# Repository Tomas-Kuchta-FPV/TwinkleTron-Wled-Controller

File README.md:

# LED Pixel Driver (TwinkleTron)

>Toto je anglická verze souboru README. Český překlad je [zde](CZ/README.md).

This project is an open-source controller for addressable LED strips, combining a wide range of features such as power measurement, IR sensors, and easy integration into various installations. The project is designed with a focus on low power consumption and user safety.

Includes:

- **ESP32-C3-WROOM-02** as the main processor.
- Integrated power measurement (ACS722 and voltage divider).
- Relay for LED power control.
- Surge and ESD protection.

## Table of Contents

0. [Introduction](#led-pixel-driver)
1. [What makes this project interesting?](#what-makes-this-project-interesting)
2. [Features](#features)
3. [Why did I decide to create this project?](#why-did-i-decide-to-create-this-project)
4. [Development](#development)
5. [Documentation](#documentation)
6. [Would I like to sell it?](#would-i-like-to-sell-it)
7. [What is my motivation?](#what-is-my-motivation)
8. [What have I learned?](#what-have-i-learned)
9. [What is its actual use?](#what-is-its-actual-use)
10. [Software](#software)
11. [Conclusion](#conclusion)
12. [Contributions](#contributions)
13. [License](#license)

### Status

- **Version**: 2.0 in the works. Evherything should be ready to order and test.

## What Makes This Project Interesting?

Power measurement!  
I wanted to know how much energy I was consuming, so I decided to use ACS722 and a voltage divider. However, I haven’t seen a similar project that includes this kind of measurement.

## Features

- ESP32-C3-WROOM-02
- Onboard relay for minimal standby current
- Integrated 10A fuse for LED strip protection
- Power measurement using WLED usermod (ACS722, voltage divider)
- Input for an external button
- Temperature sensor
- IR sensor

<details>
    <summary>Show More</summary>
    <ul>
        <li>Easy-to-use screw terminals (default)</li>
        <li>Compatible with PhoenixContact PCB connector</li>
        <li>ESP protection (PTC resettable fuse, ESD protection, diodes)</li>
        <li>Surge protection for 5V and 3.3V</li>
        <li>Boot button can be used as a WLED button</li>
        <li>Buck converter powered from Vin</li>
        <li>Unused GPIOs are exposed on the board</li>
        <li>USB-C connector</li>
        <li>5V logic output</li>
    </ul>
</details>

## Why Did I Decide to Create This Project?

I wanted to build something of my own—something I could improve and customize as needed. I also wanted to contribute to the open-source community and to create something properly designed.  
This project includes several motivations:

- **Power measurement**: To monitor energy consumption.
- **Relay**: To disconnect LED strips.
- **Low standby power**: To minimize energy usage in standby mode.
- **Ease of integration**: To simplify use in various installations.
- **To learn**: To gain experience with new technologies.
- **To share**: To contribute to the open-source community.
- **To create something nice**:  To have a functional and visually appealing solution.

## Development

I've been working on this project for quite a while.

The first prototype didn’t look great, but it worked well despite forgetting to power the SN74AHCT125 IC—something I fixed with a solder bridge.

Version V0.31 was the first to include all desired features but had a few bugs.

V1.0 was the first fully functional version but still had issues, like components on both sides of the PCB causing assembly difficulties and a suboptimal USB-voltage mixer.

V2.0 addressed all known issues and is fully functional. It is still in development, but it feels complete—though you never know what might come up. 😅

## Documentation

A great beginer video can be found here [YouTube](https://www.youtube.com/watch?v=FvPuiWTE6ic).

KiCad files are in the [Board](Board/) directory.

Schematics and PCB layouts are in the [Documentation](Documentation/) directory.  
And the [Builds](Builds/) directory contains the binary for the ESP32-C3.

The enclosure is in the [Case](Case/) directory.  
Photos of the completed project are in the [Images](Images/) directory.

## Would I Like to Sell It?

Yes, in the near future, I would like to sell this project as a finished product so that everyone can use this controller.  
It would also enable me to continue its development and create interesting new projects.

## What Is My Motivation?

- Installing LED strips in 2021.
- Problems with ESP32 (damaged power, failed updates).
- Creating a robust and user-friendly solution.

<details>
<summary>More</summary>
In 2021, I installed addressable LED strips for the first time and was amazed. However, working with bare ESP32 boards came with problems. My first controller released "magic smoke" after I accidentally applied 12V to a GPIO pin. The second ESP32 got damaged while fixing an update while still powered. These experiences inspired me to start this project.
</details>

## What Have I Learned?

I’ve learned a lot, including:

- PCB design  

<details>
<summary>More</summary>

- Using ACS722  
- Using a voltage divider  
- Using an IR sensor  
- Using a temperature sensor  
- Using a relay  
- Using a USB-C connector  
- Using a buck converter  
- Using ESP32-C3  
- Using WLED  
- Using PlatformIO  
- Using ESP-IDF  

I learned how to combine all these into a functional solution—and I enjoyed the process. 😀
</details>

## What Is Its Actual Use?

- **Controlling addressable LEDs**: Precise control of individual LEDs.
- **LED light shows**: Ideal for creating dynamic effects.  
- **Holiday decorations**: Perfect for festive displays.  
- **Easy integration**: Fits into various DIY projects.  
- **Smart home**: Great for lighting automation.

## Software

I use the `WLED` project, which is very user-friendly and feature-rich. You can download the binary [here](Builds/). My usermod is included in [GitHub PR #4108](https://github.com/Aircoookie/WLED/pull/4108). Apologies for any mistakes—I appreciate feedback. Also, I’m not experienced with Git, so I welcome patience with any errors in my PRs.

## Conclusion

This project has been both a challenge and an opportunity to push my skills forward. I’ve learned many new technologies and methods while creating a functional solution I’m proud of. The process confirmed that sharing knowledge and embracing open technologies hold great potential.

I hope this project inspires others and saves time for their own ideas. I welcome feedback, improvement suggestions, or support to continue developing this project.

Thank you for your interest I’m excited about what the future holds!

### Why Am I Doing This?

Honestly, I’m not sure I just felt inspired and supported by my family! This open-source project was born from that.

## Contributions

If you have ideas for improvements or spot errors, feel free to open a pull request or issue. All help is welcome. :)  
If anyone would like to participate in the development, I would be glad for any help. 😊  
And if anyone would like to support me financially for further development not just this project, I will be glad for any help. 😊

## License

The project is currently licensed under **CC BY-NC-SA 4.0**, allowing sharing and modifications for non-commercial use. A future transition to **CERN-OHL-S** is planned after recovering development costs.

**CC BY-NC-SA 4.0** [(CC)](https://creativecommons.org/licenses/by-nc-sa/4.0/deed.en) **→** **CERN-OHL-S** [(OSI Approved OSHW License)](https://opensource.org/license/cern-ohl-s)

Shield: [![CC BY-NC-SA 4.0][cc-by-nc-sa-shield]][cc-by-nc-sa]

This work is licensed under a
[Creative Commons Attribution-NonCommercial-ShareAlike 4.0 International License][cc-by-nc-sa].

[![CC BY-NC-SA 4.0][cc-by-nc-sa-image]][cc-by-nc-sa]

[cc-by-nc-sa]: http://creativecommons.org/licenses/by-nc-sa/4.0/
[cc-by-nc-sa-image]: https://licensebuttons.net/l/by-nc-sa/4.0/88x31.png
[cc-by-nc-sa-shield]: https://img.shields.io/badge/License-CC%20BY--NC--SA%204.0-lightgrey.svg

#### Disclaimer (No Warranty)

This licensed work is provided "as is," without any warranties, including implied warranties of merchantability or fitness for a particular purpose. The author(s) and copyright holder(s) bear no liability for claims, damages, or other liabilities.

#### AI Assistance

I used AI to assist with translation and grammar corrections. Thank you for understanding.

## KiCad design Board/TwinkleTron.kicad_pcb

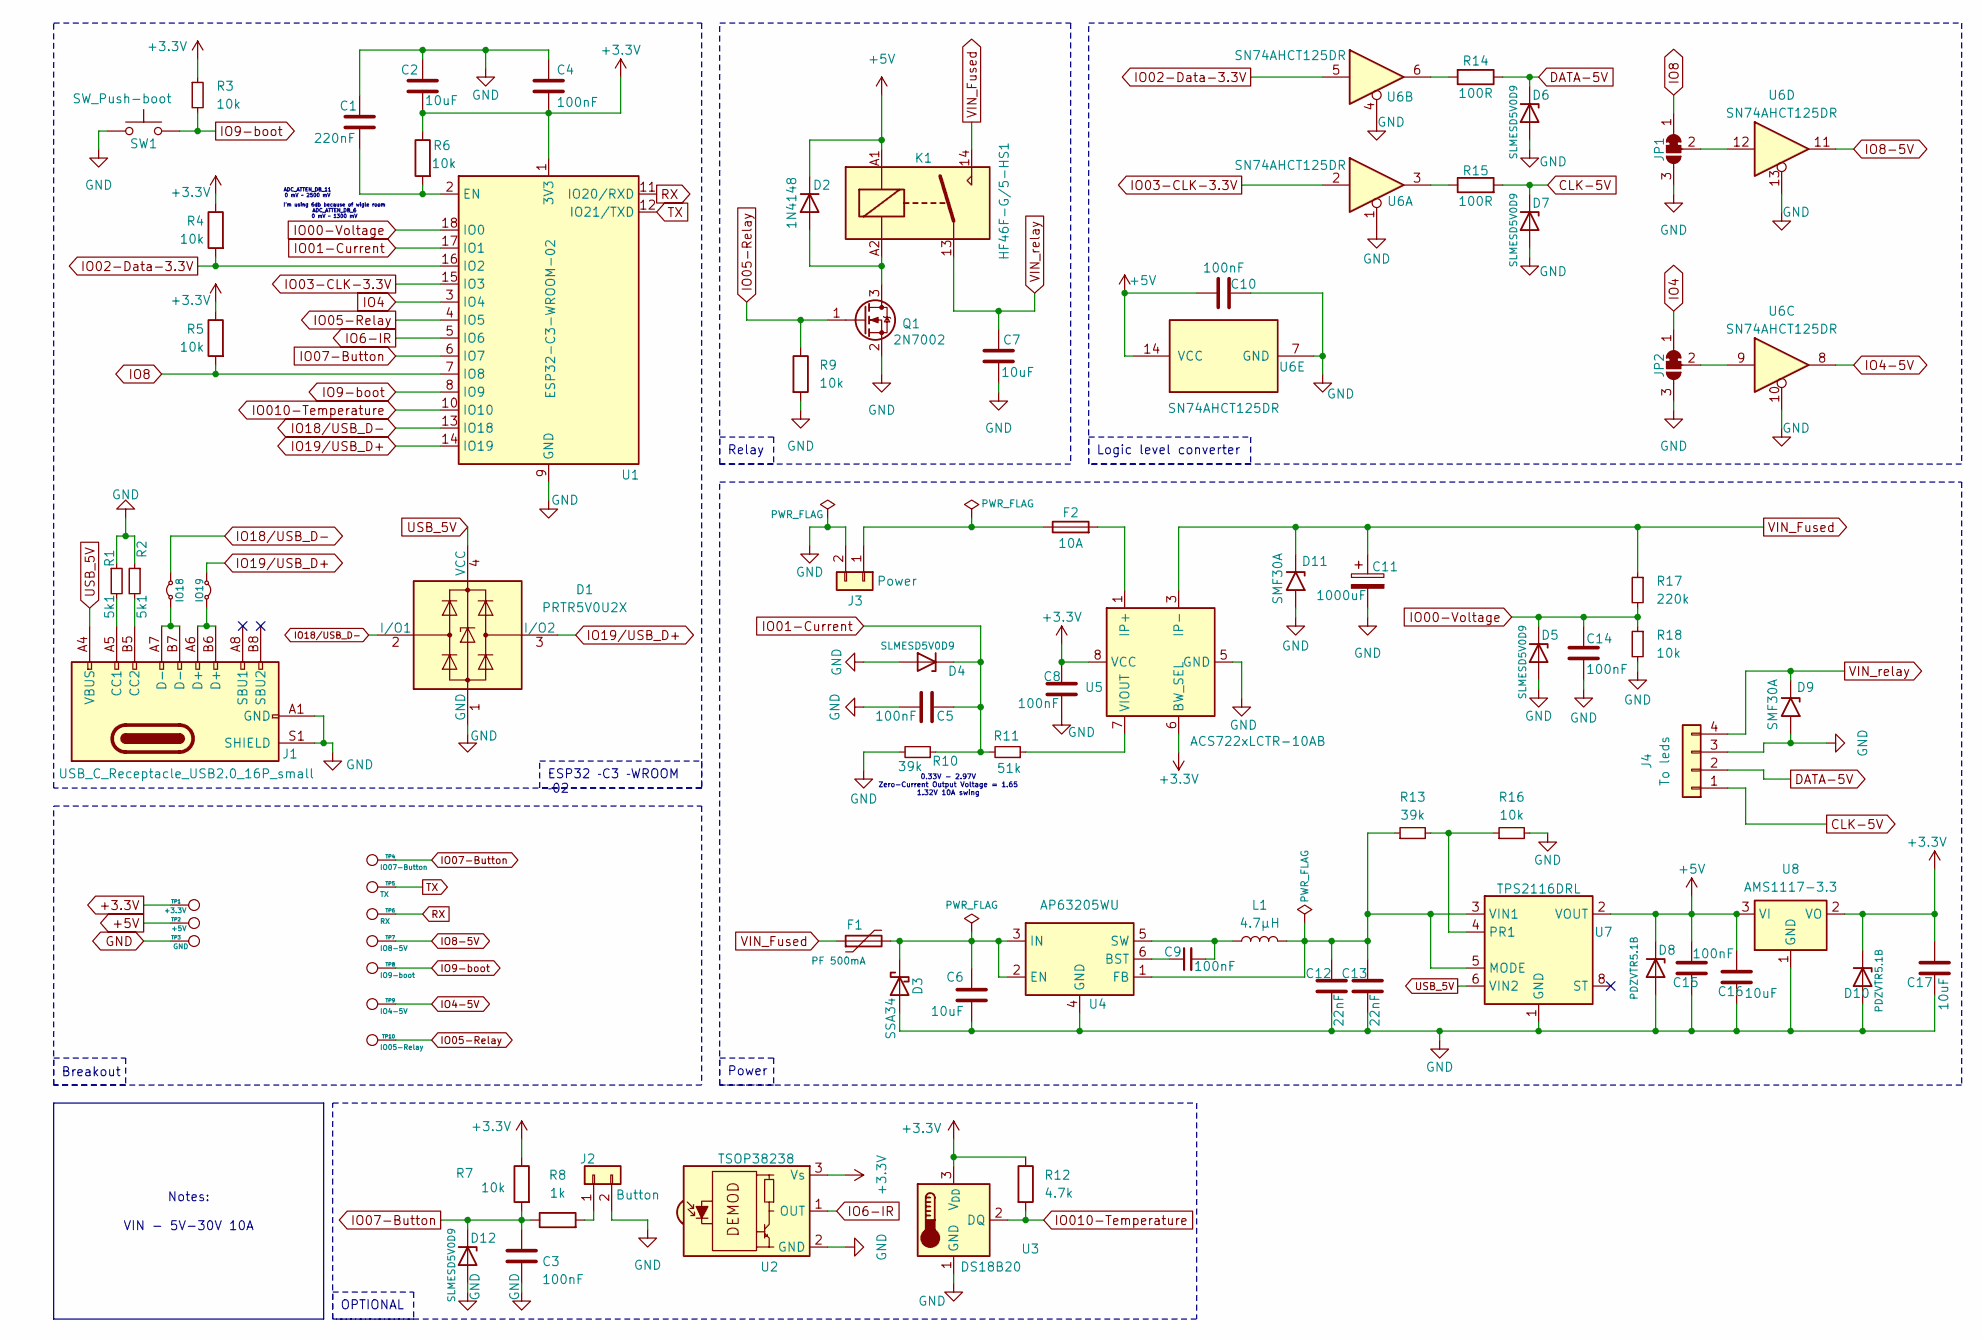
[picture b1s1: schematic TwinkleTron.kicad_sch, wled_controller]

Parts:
C1: 220nF; C_0603_1608Metric_Pad1.08x0.95mm_HandSolder; LCSC C6119866
C2, C6, C16, C17: 10uF; C_0603_1608Metric_Pad1.08x0.95mm_HandSolder; LCSC C22367827
C3, C4, C5, C8, C9, C10, C14, C15: 100nF; C_0603_1608Metric_Pad1.08x0.95mm_HandSolder; LCSC C66501
C7: 10uF; C_0603_1608Metric_Pad1.08x0.95mm_HandSolder; LCSC C194427
C11: 1000uF; CP_Radial_D10.0mm_P5.00mm_laying; LCSC C398835
C12, C13: 22nF; C_0603_1608Metric_Pad1.08x0.95mm_HandSolder; LCSC C519429
D1: PRTR5V0U2X; SOT-143; LCSC C2827688
D2: 1N4148; D_SOD-323; LCSC C2128
D3: SSA34; D_SMA; LCSC C466998
D4, D5, D6, D7, D12: SLMESD5V0D9; D_SOD-323; LCSC C19170915
D8, D10: PDZVTR5.1B; D_SOD-128; LCSC C253499
D9, D11: SMF30A; D_SMF; LCSC C19077518
F1: PF 500mA; R_1206_3216Metric_Pad1.30x1.75mm_HandSolder; LCSC C720075
F2: 10A; Fuseholder_Littelfuse_Nano2_154x; LCSC C206921
IO18, IO19: Jumper_2_Small_Bridged; SolderJumper-2_P1.3mm_Bridged_RoundedPad1.0x1.5mm
J1: USB_C_Receptacle_USB2.0_16P_small; USB_C_Receptacle_HRO_TYPE-C-31-M-12; LCSC C165948
J2: Button; PinHeader_1x02_P2.54mm_Horizontal; LCSC C492410
J3: Power; TerminalBlock_Phoenix_MKDS-3-2-5.08_1x02_P5.08mm_Horizontal; LCSC C2915639
J4: To leds; TerminalBlock_Phoenix_MKDS-3-4-5.08_1x04_P5.08mm_Horizontal; LCSC C2915641
JP1, JP2: SolderJumper_3_Bridged12; SolderJumper-3_P1.3mm_Bridged12_RoundedPad1.0x1.5mm_NumberL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
K1: HF46F-G/5-HS1; RELAY_HF46F_005-HS1; LCSC C165255
L1: 4.7µH; L_1008_2520Metric; Mfr. Part # FTC252010S4R7MBCA; LCSC C5832360
Q1: 2N7002; SOT-23; LCSC C8545
R1, R2: 5k1; R_0603_1608Metric_Pad0.98x0.95mm_HandSolder; LCSC C23186
R3, R4, R5, R6, R7, R9, R16, R18: 10k; R_0603_1608Metric_Pad0.98x0.95mm_HandSolder; LCSC C25804
R8: 1k; R_0603_1608Metric_Pad0.98x0.95mm_HandSolder; LCSC C21190
R10, R13: 39k; R_0603_1608Metric_Pad0.98x0.95mm_HandSolder; LCSC C23153
R11: 51k; R_0603_1608Metric_Pad0.98x0.95mm_HandSolder; LCSC C23196
R12: 4.7k; R_0603_1608Metric_Pad0.98x0.95mm_HandSolder; LCSC C23162
R14, R15: 100R; R_0603_1608Metric_Pad0.98x0.95mm_HandSolder; LCSC C22775
R17: 220k; R_0603_1608Metric_Pad0.98x0.95mm_HandSolder; LCSC C22961
SW1: SW_Push-boot; SW_Push_SPST_NO_Alps_SKRK; LCSC C115357
TP1: +3.3V; TestPoint_Pad_D1.5mm_SM
TP2: +5V; TestPoint_Pad_D1.5mm_SM
TP3: GND; TestPoint_Pad_D1.5mm_SM
TP4: IO07-Button; TestPoint_Pad_D1.5mm_SM
TP5: TX; TestPoint_Pad_D1.5mm_SM
TP6: RX; TestPoint_Pad_D1.5mm_SM
TP7: IO8-5V; TestPoint_Pad_D1.5mm_SM
TP8: IO9-boot; TestPoint_Pad_D1.5mm_SM
TP9: IO4-5V; TestPoint_Pad_D1.5mm_SM
TP10: IO05-Relay; TestPoint_Pad_D1.5mm_SM
U1: ESP32-C3-WROOM-02; ESP32-C3-WROOM-02-Aisler_DR; LCSC C2934560
U2: TSOP38238; Vishay_MINICAST-3Pin; LCSC C141632
U3: DS18B20; TO-92_Inline_Wide; LCSC C376006
U4: AP63205WU; TSOT-23-6; LCSC C2071056
U5: ACS722xLCTR-10AB; SOIC-8_3.9x4.9mm_P1.27mm; LCSC C459316
U6: SN74AHCT125DR; SOIC-14_3.9x8.7mm_P1.27mm; LCSC C155176
U7: TPS2116DRL; SOT-583-8; LCSC C3235557
U8: AMS1117-3.3; SOT-89-3; LCSC C880752

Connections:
+3.3V: C2.2, C4.2, C8.1, C17.1, D10.1 (K), R3.1, R4.1, R5.1, R6.1, R7.1, R12.1, TP1.1, U1.1 (3V3), U2.3 (Vs), U3.3 (V_{DD}), U5.6 (BW_SEL), U5.8 (VCC), U8.2 (VO)
+5V: C10.2, C15.1, C16.1, D2.1 (K), D8.1 (K), K1.A1, TP2.1, U6.14 (VCC), U7.2 (VOUT), U7.7 (VOUT), U8.3 (VI)
CLK-5V: D7.1 (K), J4.1, R15.2
DATA-5V: D6.1 (K), J4.2, R14.1
GND: C1.1, C2.1, C3.2, C4.1, C5.2, C6.2, C7.2, C8.2, C10.1, C11.2, C12.2, C13.2, C14.2, C15.2, C16.2, C17.2, D1.1 (GND), D3.2 (A), D4.2 (A), D5.2 (A), D6.2 (A), D7.2 (A), D8.2 (A), D9.2 (A2), D10.2 (A), D11.2 (A2), D12.2 (A), J1.A1 (GND), J1.A12 (GND), J1.B1 (GND), J1.B12 (GND), J1.S1 (SHIELD), J2.2, J3.2, J4.3, JP1.3 (B), JP2.3 (B), Q1.2 (S), R1.1, R2.1, R9.2, R10.2, R16.2, R18.2, SW1.1, TP3.1, U1.9 (GND), U1.19 (GND), U2.2 (GND), U3.1 (GND), U4.4 (GND), U5.5 (GND), U6.1, U6.4, U6.7 (GND), U6.10, U6.13, U7.1 (GND), U8.1 (GND)
IO00-Voltage: C14.1, D5.1 (K), R17.2, R18.1, U1.18 (IO0)
IO01-Current: C5.1, D4.1 (K), R10.1, R11.2, U1.17 (IO1)
IO02-Data-3.3V: R4.2, U1.16 (IO2), U6.5
IO03-CLK-3.3V: U1.15 (IO3), U6.2
IO4: JP2.1 (A), U1.3 (IO4)
IO4-5V: TP9.1, U6.8
IO05-Relay: Q1.1 (G), R9.1, TP10.1, U1.4 (IO5)
IO6-IR: U1.5 (IO6), U2.1 (OUT)
IO07-Button: C3.1, D12.1 (K), R7.2, R8.1, TP4.1, U1.6 (IO7)
IO8: JP1.1 (A), R5.2, U1.7 (IO8)
IO8-5V: TP7.1, U6.11
IO9-boot: R3.2, SW1.2, TP8.1, U1.8 (IO9)
IO010-Temperature: R12.2, U1.10 (IO10), U3.2 (DQ)
IO18/USB_D-: D1.2 (I/O1), IO18.2 (B), U1.13 (IO18)
IO19/USB_D+: D1.3 (I/O2), IO19.2 (B), U1.14 (IO19)
unnamed: D2.2 (A), K1.A2, Q1.3 (D)
unnamed: C6.1, D3.1 (K), F1.2, U4.2 (EN), U4.3 (IN)
unnamed: F2.2, U5.1 (IP+), U5.2 (IP+)
unnamed: IO18.1 (A), J1.A7 (D-), J1.B7 (D-)
unnamed: IO19.1 (A), J1.A6 (D+), J1.B6 (D+)
unnamed: J1.A5 (CC1), R1.2
unnamed: J1.B5 (CC2), R2.2
unnamed: J2.1, R8.2
unnamed: F2.1, J3.1
unnamed: JP1.2 (C), U6.12
unnamed: JP2.2 (C), U6.9
unnamed: R14.2, U6.6
unnamed: R15.1, U6.3
unnamed: C1.2, R6.2, U1.2 (EN)
unnamed: C9.1, U4.6 (BST)
unnamed: C12.1, C13.1, L1.2, R13.1, U4.1 (FB), U7.3 (VIN1), U7.5 (MODE)
unnamed: C9.2, L1.1, U4.5 (SW)
unnamed: R11.1, U5.7 (VIOUT)
unnamed: R13.2, R16.1, U7.4 (PR1)
RX: TP6.1, U1.11 (IO20/RXD)
TX: TP5.1, U1.12 (IO21/TXD)
USB_5V: D1.4 (VCC), J1.A4 (VBUS), J1.A9 (VBUS), J1.B4 (VBUS), J1.B9 (VBUS), U7.6 (VIN2)
VIN_Fused: C11.1, D11.1 (A1), F1.1, K1.14, R17.1, U5.3 (IP-), U5.4 (IP-)
VIN_relay: C7.1, D9.1 (A1), J4.4, K1.13

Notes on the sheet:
Notes: VIN - 5V-30V 10A
Relay
Breakout
ESP32 ­C3 ­WROOM ­02
Power
OPTIONAL
Logic level converter
ADC_ATTEN_DB_11 0 mV ~ 2500 mV
0.33V - 2.97V Zero-Current Output Voltage = 1.65 1.32V 10A swing
I'm using 6db because of wigle room ADC_ATTEN_DB_6 0 mV ~ 1300 mV

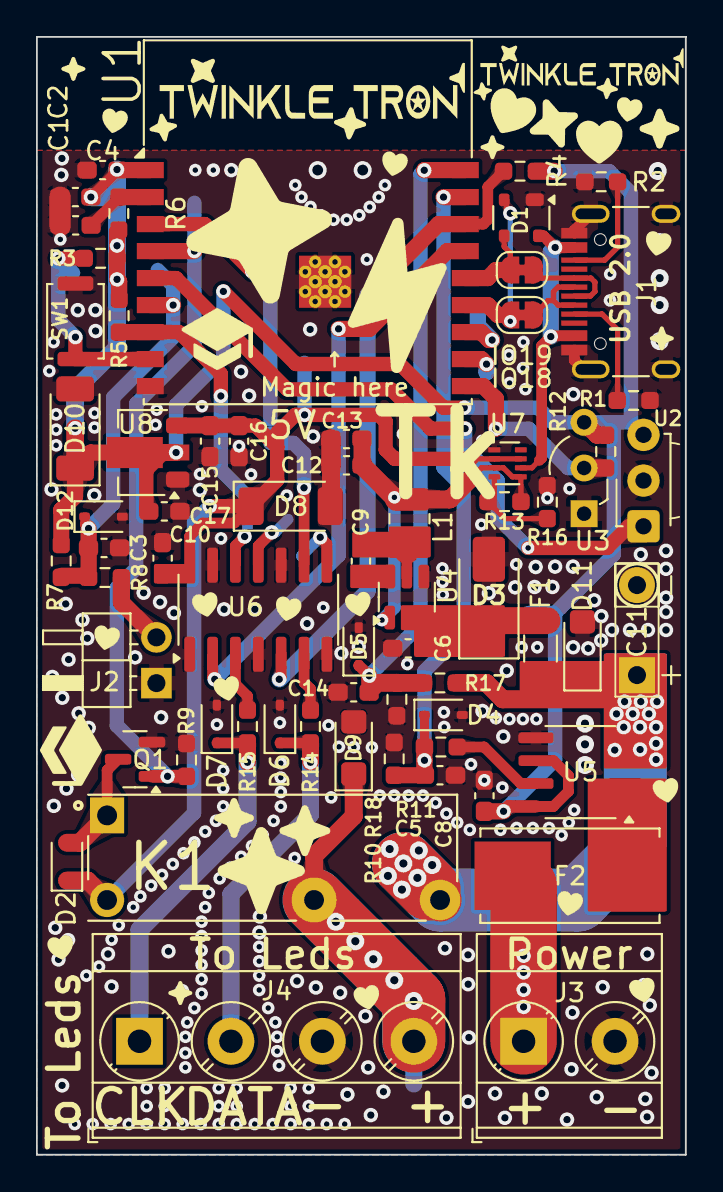
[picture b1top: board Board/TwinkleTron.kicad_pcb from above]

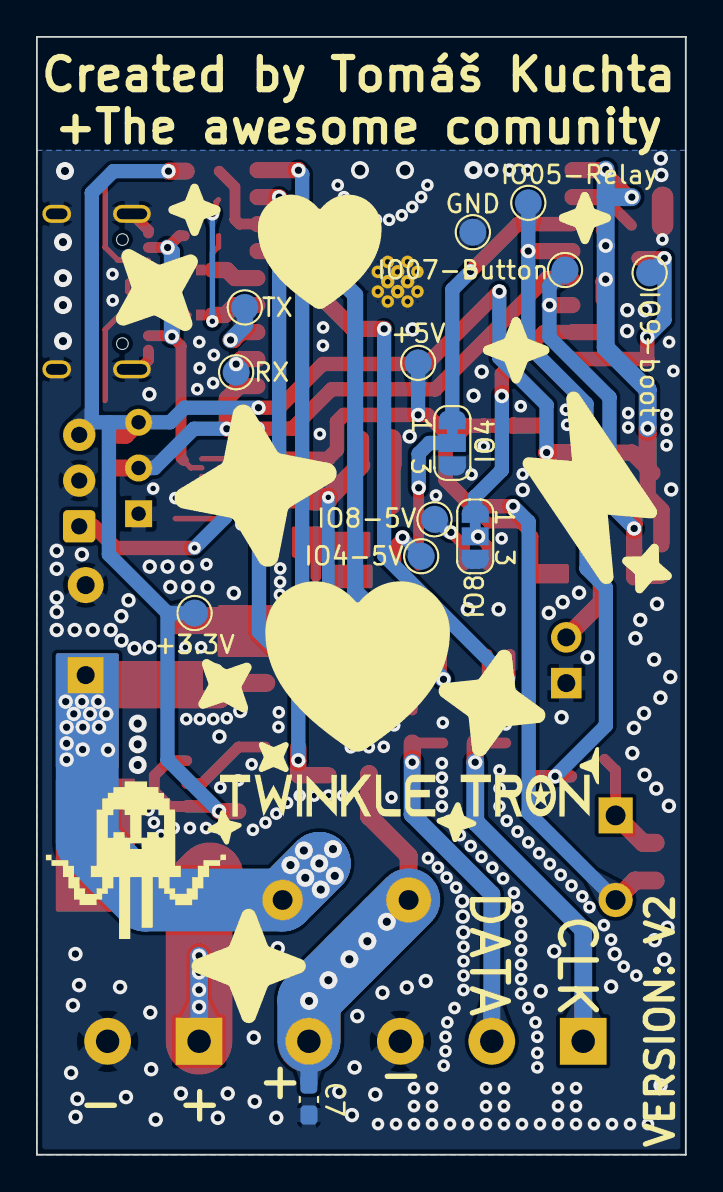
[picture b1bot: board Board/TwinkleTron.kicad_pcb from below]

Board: 2 copper layers, 36.0 x 62.1 mm, 83 parts (15 on the bottom side), 44 nets.

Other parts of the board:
akemi001: LOGO; akemi
logo1, logo2, logo3: LOGO; logo

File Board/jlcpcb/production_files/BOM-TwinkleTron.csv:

Comment,Designator,Footprint,LCSC
TSOP38238,U2,Vishay_MINICAST-3Pin,C141632
SN74AHCT125DR,U6,SOIC-14_3.9x8.7mm_P1.27mm,C155176
HF46F-G/5-HS1,K1,RELAY_HF46F_005-HS1,C165255
USB_C_Receptacle_USB2.0_16P_small,J1,USB_C_Receptacle_HRO_TYPE-C-31-M-12,C165948
SMF30A,D9,D_SMF,C19077518
SLMESD5V0D9,"D4,D5,D6,D7",D_SOD-323,C19170915
10uF,C7,C_0603_1608Metric_Pad1.08x0.95mm_HandSolder,C194427
10A,F2,Fuseholder_Littelfuse_Nano2_154x,C206921
AP63205WU,U4,TSOT-23-6,C2071056
1k,R8,R_0603_1608Metric_Pad0.98x0.95mm_HandSolder,C21190
1N4148,D2,D_SOD-323,C2128
10uF,"C16,C17,C2,C6",C_0603_1608Metric_Pad1.08x0.95mm_HandSolder,C22367827
100R,"R14,R15",R_0603_1608Metric_Pad0.98x0.95mm_HandSolder,C22775
220k,R17,R_0603_1608Metric_Pad0.98x0.95mm_HandSolder,C22961
39k,"R10,R13",R_0603_1608Metric_Pad0.98x0.95mm_HandSolder,C23153
4.7k,R12,R_0603_1608Metric_Pad0.98x0.95mm_HandSolder,C23162
5k1,"R1,R2",R_0603_1608Metric_Pad0.98x0.95mm_HandSolder,C23186
51k,R11,R_0603_1608Metric_Pad0.98x0.95mm_HandSolder,C23196
PDZVTR5.1B,"D10,D8",D_SOD-128,C253499
10k,"R16,R18,R3,R4,R5,R6,R7,R9",R_0603_1608Metric_Pad0.98x0.95mm_HandSolder,C25804
PRTR5V0U2X,D1,SOT-143,C2827688
Power,J3,TerminalBlock_Phoenix_MKDS-3-2-5.08_1x02_P5.08mm_Horizontal,C2915639
To leds,J4,TerminalBlock_Phoenix_MKDS-3-4-5.08_1x04_P5.08mm_Horizontal,C2915641
ESP32-C3-WROOM-02,U1,ESP32-C3-WROOM-02-Aisler_DR,C2934560
TPS2116DRL,U7,SOT-583-8,C3235557
DS18B20,U3,TO-92_Inline_Wide,C376006
1000uF,C11,CP_Radial_D10.0mm_P5.00mm_laying,C398835
ACS722xLCTR-10AB,U5,SOIC-8_3.9x4.9mm_P1.27mm,C459316
SSA34,D3,D_SMA,C466998
Button,J2,PinHeader_1x02_P2.54mm_Horizontal,C492410
22nF,"C12,C13",C_0603_1608Metric_Pad1.08x0.95mm_HandSolder,C519429
4.7µH,L1,L_1008_2520Metric,C5832360
220nF,C1,C_0603_1608Metric_Pad1.08x0.95mm_HandSolder,C6119866
100nF,"C10,C14,C15,C3,C4,C5,C8,C9",C_0603_1608Metric_Pad1.08x0.95mm_HandSolder,C66501
PF 500mA,F1,R_1206_3216Metric_Pad1.30x1.75mm_HandSolder,C720075
AMS1117-3.3,U8,SOT-89-3,C880752
SW_Push-boot,SW1,SW_Push_SPST_NO_Alps_SKRK,
2N7002,Q1,SOT-23,

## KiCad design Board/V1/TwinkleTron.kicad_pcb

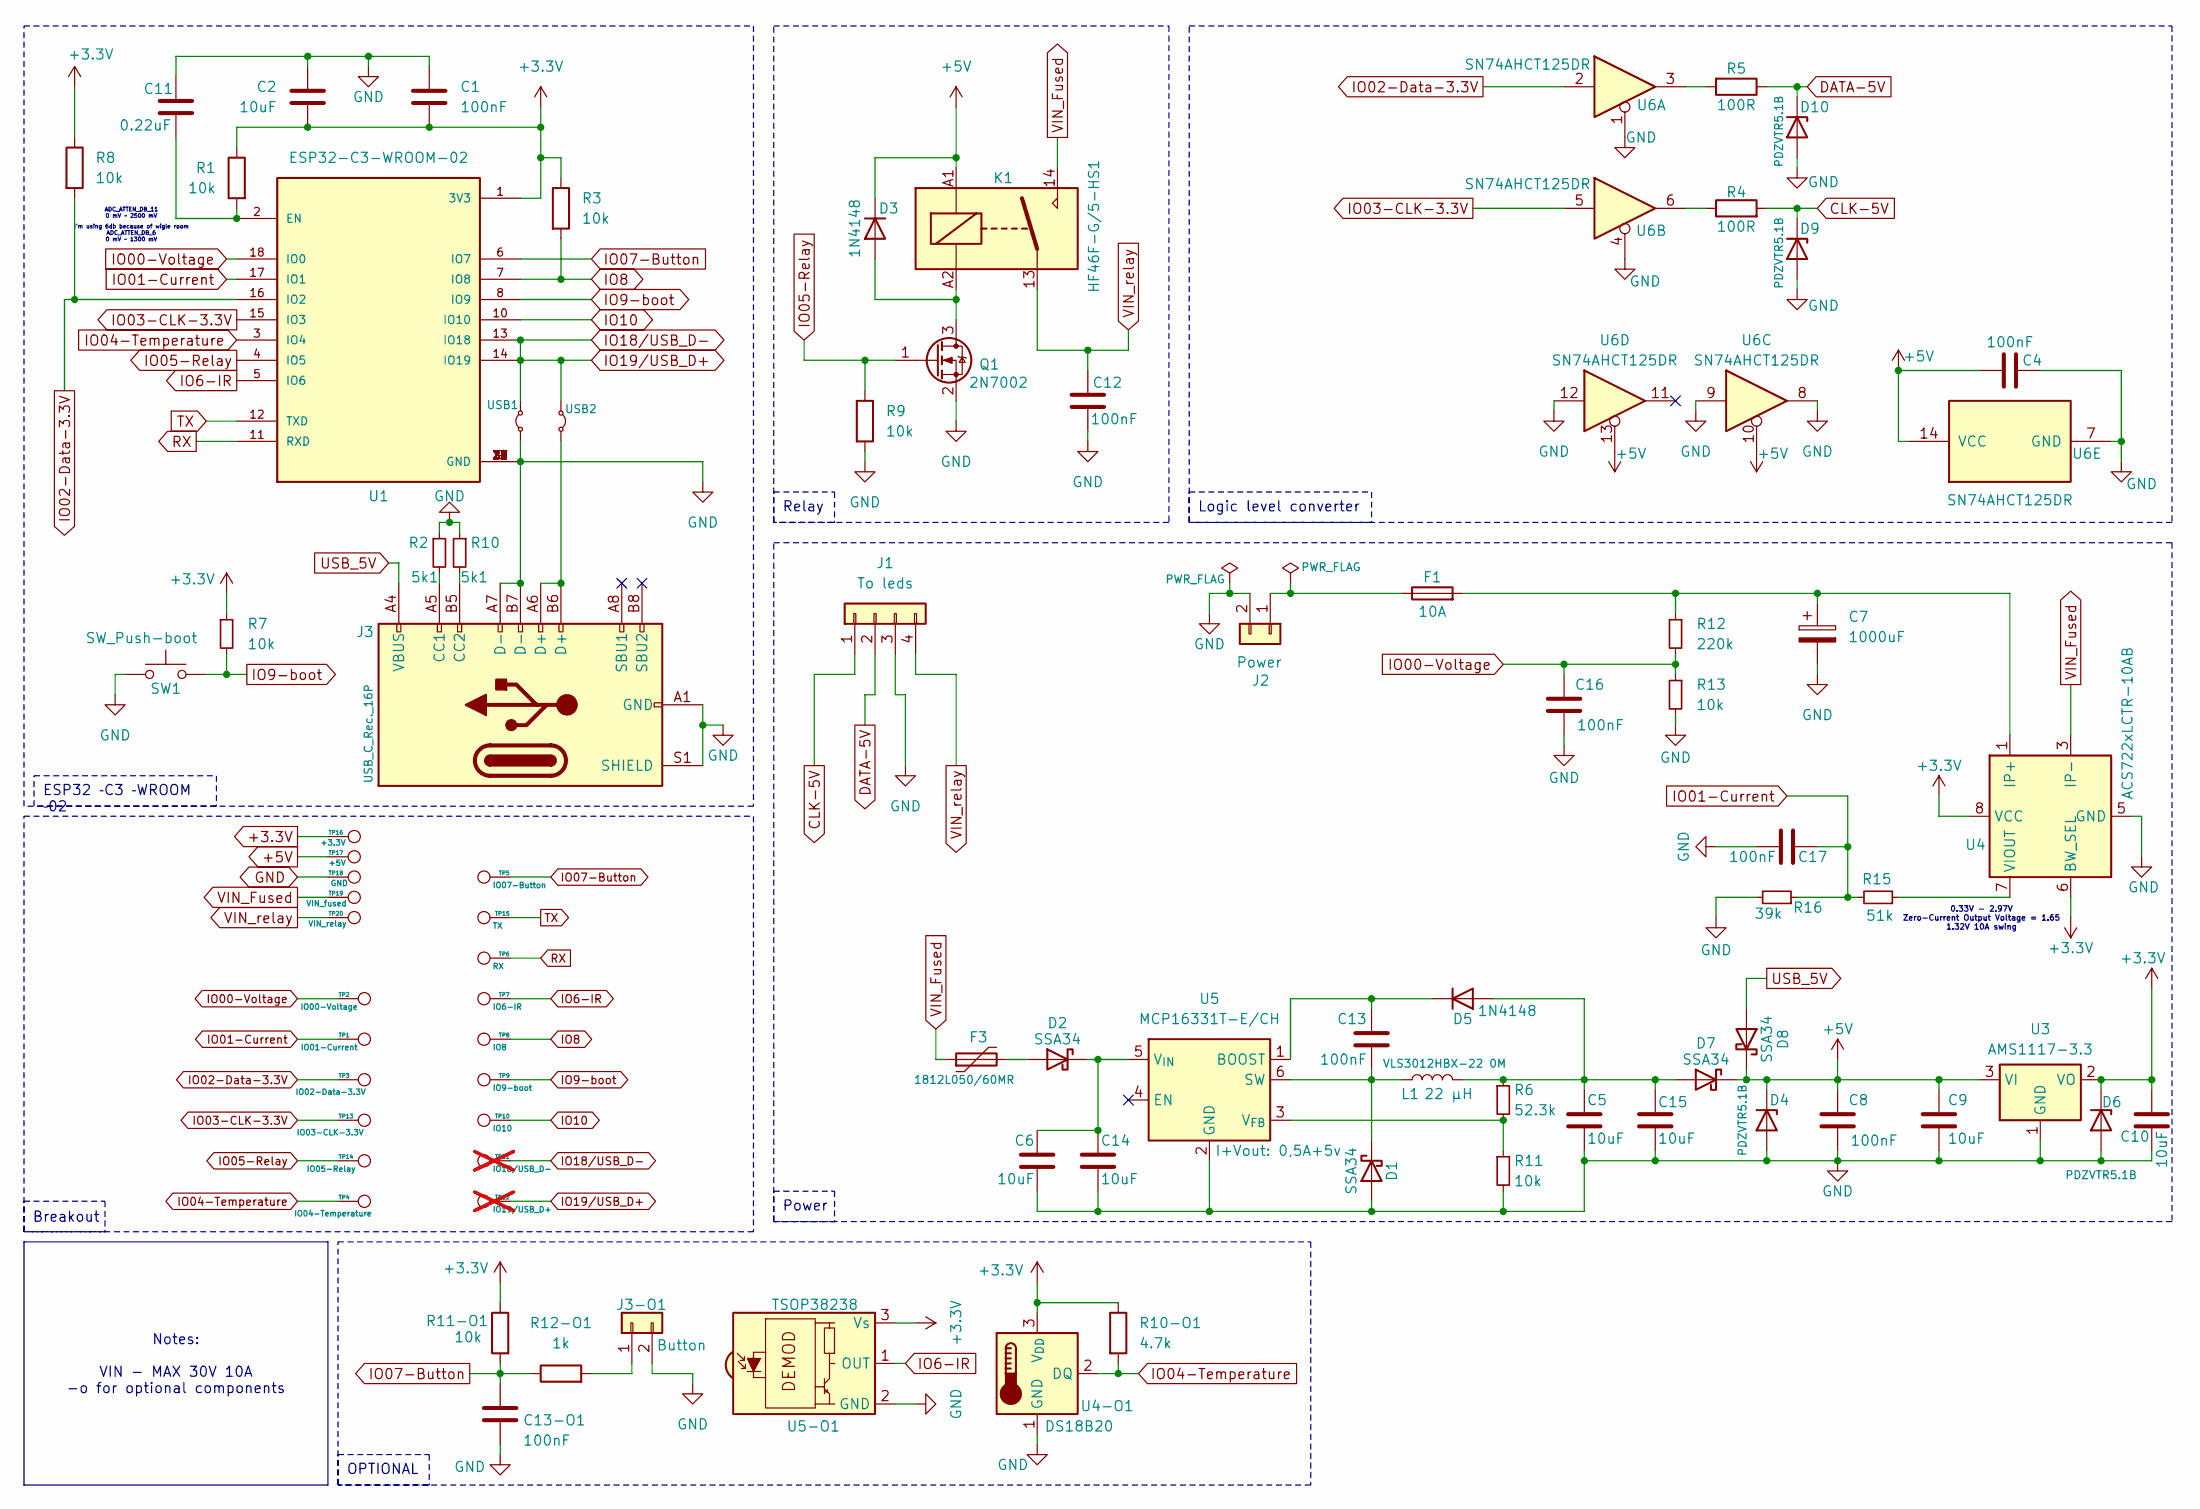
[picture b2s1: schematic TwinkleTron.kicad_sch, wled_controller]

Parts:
C1, C4, C8, C12, C13, C13-O1, C16, C17: 100nF; C_0805_2012Metric_Pad1.18x1.45mm_HandSolder
C2, C5, C6, C9, C10, C14, C15: 10uF; C_0805_2012Metric_Pad1.18x1.45mm_HandSolder
C7: 1000uF; CP_Radial_D10.0mm_P5.00mm
C11: 0.22uF; C_0805_2012Metric_Pad1.18x1.45mm_HandSolder
D1, D2, D7, D8: SSA34; D_SMA_Handsoldering
D3, D5: 1N4148; D_SOD-123
D4, D6, D9, D10: PDZVTR5.1B; D_SOD-128
F1: 10A; Fuseholder_Littelfuse_Nano2_154x
F3: 1812L050/60MR; FUSE_1812L200_12DR
J1: To leds
J2: Power
J3: USB_C_Rec._16P; USB_C_Receptacle_HRO_TYPE-C-31-M-12; LCSC C165948
J3-O1: Button; JST_XH_S2B-XH-A_1x02_P2.50mm_Horizontal
K1: HF46F-G/5-HS1; RELAY_HF46F_005-HS1
L1: 22 µH; IND_VLS3012HBX-220M; MPN VLS3012HBX-22 0M
Q1: 2N7002; SOT-23
R1, R3, R7, R8, R9, R11, R11-O1, R13: 10k; R_0805_2012Metric_Pad1.20x1.40mm_HandSolder
R2, R10: 5k1; R_0805_2012Metric_Pad1.20x1.40mm_HandSolder
R4, R5: 100R; R_0805_2012Metric_Pad1.20x1.40mm_HandSolder
R6: 52.3k; R_0805_2012Metric_Pad1.20x1.40mm_HandSolder
R10-O1: 4.7k; R_0805_2012Metric_Pad1.20x1.40mm_HandSolder
R12: 220k; R_0805_2012Metric_Pad1.20x1.40mm_HandSolder
R12-O1: 1k; R_0805_2012Metric_Pad1.20x1.40mm_HandSolder
R15: 51k; R_0805_2012Metric_Pad1.20x1.40mm_HandSolder
R16: 39k; R_0805_2012Metric_Pad1.20x1.40mm_HandSolder
SW1: SW_Push-boot; SW_Push_SPST_NO_Alps_SKRK
TP1: IO01-Current; TestPoint_Pad_D2.0mm
TP2: IO00-Voltage; TestPoint_Pad_D2.0mm
TP3: IO02-Data-3.3V; TestPoint_Pad_D2.0mm
TP4: IO04-Temperature; TestPoint_Pad_D2.0mm
TP5: IO07-Button; TestPoint_Pad_D2.0mm
TP6: RX; TestPoint_Pad_D2.0mm
TP7: IO6-IR; TestPoint_Pad_D2.0mm
TP8: IO8; TestPoint_Pad_D2.0mm
TP9: IO9-boot; TestPoint_Pad_D2.0mm
TP10: IO10; TestPoint_Pad_D2.0mm
TP11: IO18/USB_D-; TestPoint_Pad_D2.0mm; not fitted
TP12: IO19/USB_D+; TestPoint_Pad_D2.0mm; not fitted
TP13: IO03-CLK-3.3V; TestPoint_Pad_D2.0mm
TP14: IO05-Relay; TestPoint_Pad_D2.0mm
TP15: TX; TestPoint_Pad_D2.0mm
TP16: +3.3V; TestPoint_Pad_D2.0mm
TP17: +5V; TestPoint_Pad_D2.0mm
TP18: GND; TestPoint_Pad_D2.0mm
TP19: VIN_fused; TestPoint_Pad_D2.0mm
TP20: VIN_relay; TestPoint_Pad_D2.0mm
U1: ESP32-C3-WROOM-02; LCSC C2934560
U3: AMS1117-3.3; SOT-223-3_TabPin2
U4: ACS722xLCTR-10AB; SOIC-8_3.9x4.9mm_P1.27mm
U4-O1: DS18B20; TO-92_Inline
U5: MCP16331T-E/CH; SOT-23-6_Handsoldering
U5-O1: TSOP38238; Vishay_MINICAST-3Pin
U6: SN74AHCT125DR; SOIC-14_3.9x8.7mm_P1.27mm
USB1, USB2: Jumper_2_Small_Bridged; SolderJumper-2_P1.3mm_Bridged_RoundedPad1.0x1.5mm

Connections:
+3.3V: C1.2, C2.2, C10.1, D6.1 (K), R1.1, R3.1, R7.1, R8.1, R10-O1.1, R11-O1.1, TP16.1, U1.1 (3V3), U3.2 (VO), U4.6 (BW_SEL), U4.8 (VCC), U4-O1.3 (V_{DD}), U5-O1.3 (Vs)
+5V: C4.2, C8.1, C9.1, D3.1 (K), D4.1 (K), D7.1 (K), D8.1 (K), K1.A1, TP17.1, U3.3 (VI), U6.10, U6.13, U6.14 (VCC)
+VIN: F1.1, J2.1
CLK-5V: D9.1 (K), J1.1, R4.2
DATA-5V: D10.1 (K), J1.2, R5.1
IO00-Voltage: C16.1, R12.2, R13.1, TP2.1, U1.18 (IO0)
IO01-Current: C17.1, R15.2, R16.1, TP1.1, U1.17 (IO1)
IO02-Data-3.3V: R8.2, TP3.1, U1.16 (IO2), U6.2
IO03-CLK-3.3V: TP13.1, U1.15 (IO3), U6.5
IO04-Temperature: R10-O1.2, TP4.1, U1.3 (IO4), U4-O1.2 (DQ)
IO05-Relay: Q1.1 (G), R9.1, TP14.1, U1.4 (IO5)
IO6-IR: TP7.1, U1.5 (IO6), U5-O1.1 (OUT)
IO07-Button: C13-O1.1, R11-O1.2, R12-O1.1, TP5.1, U1.6 (IO7)
IO8: R3.2, TP8.1, U1.7 (IO8)
IO9-boot: R7.2, SW1.2, TP9.1, U1.8 (IO9)
IO10: TP10.1, U1.10 (IO10)
unnamed: C7.1, F1.2, R12.1, U4.1 (IP+), U4.2 (IP+)
unnamed: C13.2, D1.1 (K), L1.1, U5.6 (SW)
unnamed: D2.2 (A), F3.2
unnamed: C6.1, C14.1, D2.1 (K), U5.5 (V_{IN})
unnamed: D3.2 (A), K1.A2, Q1.3 (D)
unnamed: C5.1, C15.1, D5.2 (A), D7.2 (A), L1.2, R6.1
unnamed: C13.1, D5.1 (K), U5.1 (BOOST)
unnamed: J3.A5 (CC1), R2.2
unnamed: J3.B5 (CC2), R10.2
unnamed: J3-O1.1, R12-O1.2
unnamed: R4.1, U6.6
unnamed: R5.2, U6.3
unnamed: C11.2, R1.2, U1.2 (EN)
unnamed: R15.1, U4.7 (VIOUT)
unnamed: R6.2, R11.1, U5.3 (V_{FB})
unnamed: J3.A6 (D+), J3.B6 (D+), USB2.1 (A)
RX: TP6.1, U1.11 (RXD)
TX: TP15.1, U1.12 (TXD)
USB_5V: D8.2 (A), J3.A4 (VBUS), J3.A9 (VBUS), J3.B4 (VBUS), J3.B9 (VBUS)
VIN_Fused: F3.1, K1.14, TP19.1, U4.3 (IP-), U4.4 (IP-)
VIN_relay: C12.1, J1.4, K1.13, TP20.1

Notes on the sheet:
Notes: VIN - MAX 30V 10A -o for optional components
Relay
Breakout
ESP32 ­C3 ­WROOM ­02
Power
OPTIONAL
Logic level converter
ADC_ATTEN_DB_11 0 mV ~ 2500 mV
0.33V - 2.97V Zero-Current Output Voltage = 1.65 1.32V 10A swing
I'm using 6db because of wigle room ADC_ATTEN_DB_6 0 mV ~ 1300 mV

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
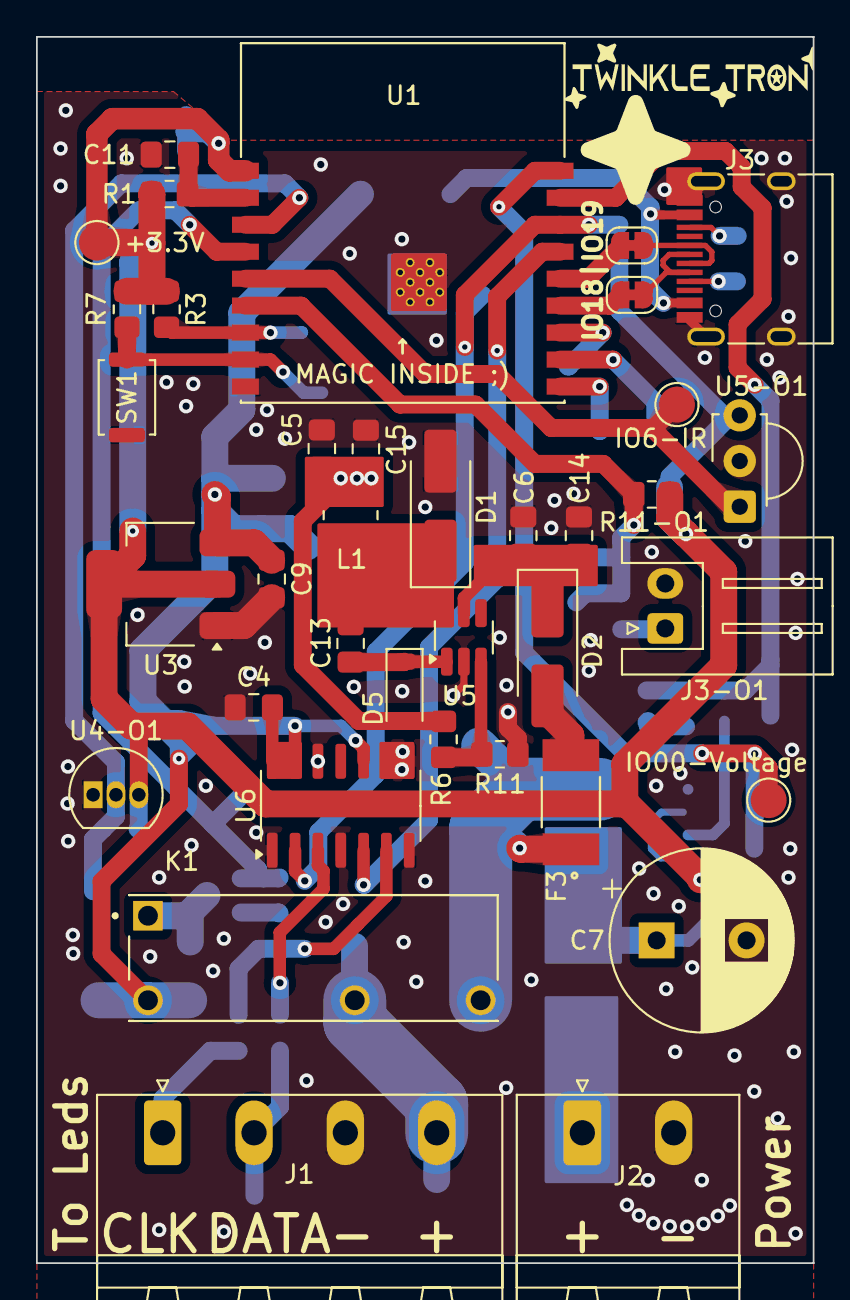
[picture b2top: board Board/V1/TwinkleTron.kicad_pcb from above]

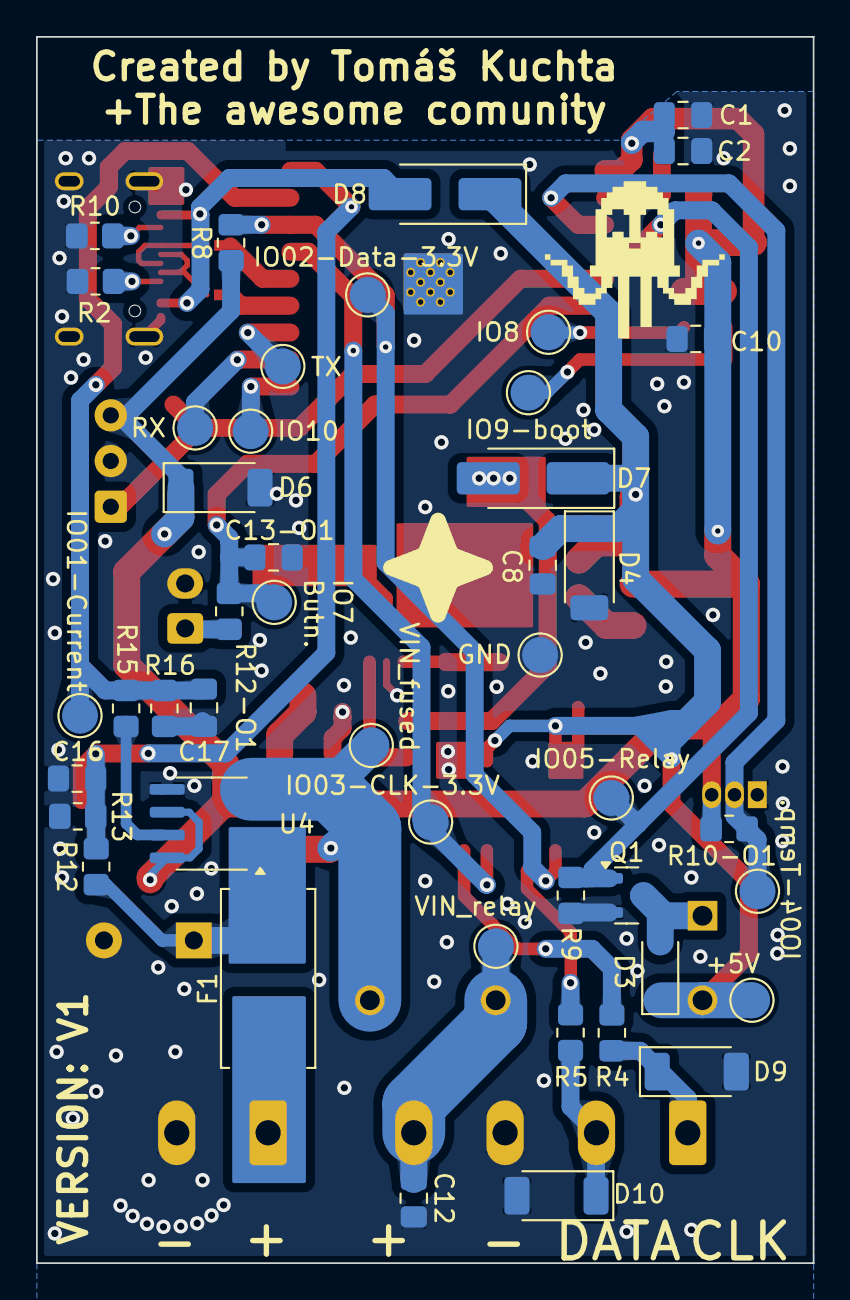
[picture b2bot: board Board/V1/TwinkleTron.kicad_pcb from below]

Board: 2 copper layers, 43.2 x 68.2 mm, 82 parts (45 on the bottom side), 41 nets.

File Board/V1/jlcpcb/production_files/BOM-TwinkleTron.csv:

Comment,Designator,Footprint,LCSC
USB_C_Rec._16P,J3,USB_C_Receptacle_HRO_TYPE-C-31-M-12,C165948
ESP32-C3-WROOM-02,U1,ESP32-C3-WROOM-02,C2934560
100nF,C13,C_0805_2012Metric_Pad1.18x1.45mm_HandSolder,
10k,R1,R_0805_2012Metric_Pad1.20x1.40mm_HandSolder,
TSOP38238,U5-O1,Vishay_MINICAST-3Pin,
10uF,C9,C_0805_2012Metric_Pad1.18x1.45mm_HandSolder,
10uF,C6,C_0805_2012Metric_Pad1.18x1.45mm_HandSolder,
10k,R11-O1,R_0805_2012Metric_Pad1.20x1.40mm_HandSolder,
10k,R11,R_0805_2012Metric_Pad1.20x1.40mm_HandSolder,
HF46F-G/5-HS1,K1,RELAY_HF46F_005-HS1,
AMS1117-3.3,U3,SOT-223-3_TabPin2,
10uF,C14,C_0805_2012Metric_Pad1.18x1.45mm_HandSolder,
10k,R7,R_0805_2012Metric_Pad1.20x1.40mm_HandSolder,
MCP16331T-E/CH,U5,SOT-23-6_Handsoldering,
To leds,J1,"PhoenixContact_MSTBA_2,5_4-G-5,08_1x04_P5.08mm_Horizontal",
DS18B20,U4-O1,TO-92_Inline,
52.3k,R6,R_0805_2012Metric_Pad1.20x1.40mm_HandSolder,
100nF,C4,C_0805_2012Metric_Pad1.18x1.45mm_HandSolder,
10uF,C5,C_0805_2012Metric_Pad1.18x1.45mm_HandSolder,
22 µH,L1,IND_VLS3012HBX-220M,
10k,R3,R_0805_2012Metric_Pad1.20x1.40mm_HandSolder,
SN74AHCT125DR,U6,SOIC-14_3.9x8.7mm_P1.27mm,
Power,J2,"PhoenixContact_MSTBA_2,5_2-G-5,08_1x02_P5.08mm_Horizontal",
1000uF,C7,CP_Radial_D10.0mm_P5.00mm,
SSA34,D1,D_SMA_Handsoldering,
SSA34,D2,D_SMA_Handsoldering,
1N4148,D5,D_SOD-123,
Button,J3-O1,JST_XH_S2B-XH-A_1x02_P2.50mm_Horizontal,
0.22uF,C11,C_0805_2012Metric_Pad1.18x1.45mm_HandSolder,
1812L050/60MR,F3,FUSE_1812L200_12DR,
SW_Push-boot,SW1,SW_Push_SPST_NO_Alps_SKRK,
10uF,C15,C_0805_2012Metric_Pad1.18x1.45mm_HandSolder,
100nF,C17,C_0805_2012Metric_Pad1.18x1.45mm_HandSolder,
PDZVTR5.1B,D4,D_SOD-128,
PDZVTR5.1B,D9,D_SOD-128,
SSA34,D7,D_SMA_Handsoldering,
220k,R12,R_0805_2012Metric_Pad1.20x1.40mm_HandSolder,
51k,R15,R_0805_2012Metric_Pad1.20x1.40mm_HandSolder,
PDZVTR5.1B,D6,D_SOD-128,
1N4148,D3,D_SOD-123,
100nF,C1,C_0805_2012Metric_Pad1.18x1.45mm_HandSolder,
10k,R8,R_0805_2012Metric_Pad1.20x1.40mm_HandSolder,
ACS722xLCTR-10AB,U4,SOIC-8_3.9x4.9mm_P1.27mm,
4.7k,R10-O1,R_0805_2012Metric_Pad1.20x1.40mm_HandSolder,
39k,R16,R_0805_2012Metric_Pad1.20x1.40mm_HandSolder,
100nF,C16,C_0805_2012Metric_Pad1.18x1.45mm_HandSolder,
10k,R13,R_0805_2012Metric_Pad1.20x1.40mm_HandSolder,
2N7002,Q1,SOT-23,
100nF,C8,C_0805_2012Metric_Pad1.18x1.45mm_HandSolder,
100R,R5,R_0805_2012Metric_Pad1.20x1.40mm_HandSolder,
10A,F1,Fuseholder_Littelfuse_Nano2_154x,
1k,R12-O1,R_0805_2012Metric_Pad1.20x1.40mm_HandSolder,
5k1,R2,R_0805_2012Metric_Pad1.20x1.40mm_HandSolder,
10uF,C10,C_0805_2012Metric_Pad1.18x1.45mm_HandSolder,
10k,R9,R_0805_2012Metric_Pad1.20x1.40mm_HandSolder,
100nF,C12,C_0805_2012Metric_Pad1.18x1.45mm_HandSolder,
5k1,R10,R_0805_2012Metric_Pad1.20x1.40mm_HandSolder,
SSA34,D8,D_SMA_Handsoldering,
100R,R4,R_0805_2012Metric_Pad1.20x1.40mm_HandSolder,
100nF,C13-O1,C_0805_2012Metric_Pad1.18x1.45mm_HandSolder,
PDZVTR5.1B,D10,D_SOD-128,
10uF,C2,C_0805_2012Metric_Pad1.18x1.45mm_HandSolder,

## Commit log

2024-08-14 synced with my local repo
    VERSION: V0.4
2024-11-21 Improve repository aesthetics
